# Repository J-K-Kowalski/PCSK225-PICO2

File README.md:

# PCSK225-PICO2 SDR Receiver

<ul>
<li>2025-08-27 - Documentation</li>
<li>2025-02-25 - First version of the project</li>
</ul>

## Overview

<p>PCSK225-PICO2 is a compact, low‑cost software defined receiver designed to decode the 225 kHz Polish time signal transmitted from Solec Kujawski. The design is built around the Raspberry Pi Pico 2 (RP2350) module and supports two signal acquisition paths:

- Direct sampling with a high‑speed external ADC (ADS7049)
- Optional SSB down‑conversion using a Si4537‑D60 tuner, enabling baseband sampling with the RP2350’s internal ADC

<p>The board integrates a precision RTC, local display, I/O expansion, audio output, and multiple user I/Os, making it a self‑contained platform for time‑signal experiments and SDR development.

## Key Features

- MCU: Raspberry Pi Pico 2 (RP2350) module
- Direct RF sampling: ADS7049 12‑bit, high‑speed SPI ADC connected to the RP2350 (supports ~225 kHz IF/baseband sampling)
- Optional tuner: Si4537‑D60 for SSB-style down‑conversion to low IF/baseband for sampling by the RP2350 internal ADC
- RF front end:
    - Active 6‑pole Butterworth band‑pass amplifier around TLV9064 (U2) centered on 225 kHz
    - Output/driver amplifier for Si4537 based on TLV9062 (U1)
    - TMUX1204 analog multiplexer (IC1) for flexible signal routing between ADCs and front‑end nodes
- Timing: DS3231 RTC with CR2032 backup battery for stable timekeeping and 1 Hz/32 kHz outputs
- Displays:
    - On‑board 0.96" I2C OLED (SSD1306)
    - Header for an external graphic LCD
- I/O expansion and storage:
    - PCA9500 I2C port expander with integrated EEPROM for configuration storage
- Connectivity and power:
    - Micro‑USB (Pico 2)
    - USB‑C connector for powering the receiver and PC connectivity
- User I/O:
    - 8 general‑purpose digital I/O lines on headers
    - PWM‑driven speaker/buzzer output with buffer stage
- Form factor: single PCB with Pico 2 module, mounting holes, and on‑board connectors
- See pcb.jpg for a 3D view of the assembled board

## Signal Paths

- Direct 225 kHz path:

1) Antenna/RF input → active BPF (U2 TLV9064) → analog mux (IC1) → ADS7049 → RP2350 via SPI/DMA
2) Intended for coherent sampling/decoding of the Polish 225 kHz time code
- Optional SSB/down‑conversion path:

1) RF input → Si4537‑D60 → low‑IF/baseband → output amplifier (U1 TLV9062) → RP2350 internal ADC
2) Useful for alternative demodulation modes and experiments

## Subsystem Details

- Active BPF: 6‑pole Butterworth around 225 kHz using TLV9064 quad op‑amp, input protection, and gain‑setting network
- Analog MUX: TMUX1204 routes filtered RF to the external ADC or other measurement points
- External ADC: ADS7049 low‑latency, SPI, suited for continuous streaming to RP2350 (DMA recommended)
- RTC: DS3231SN provides INT/SQW and 32 kHz outputs; backed by CR2032 cell
- Displays:
    - SSD1306 OLED on I2C bus (address configurable via jumpers)
    - External LCD header with SPI/I2C signals as routed on the schematic
- I2C Expander/EEPROM: PCA9500 provides extra GPIO and non‑volatile storage for calibration and user settings
- Audio: small speaker output driven from MCU PWM through a buffer (74LVC1G34) and filtering
- Power:
    - 3V3 rail with local decoupling (X5R/COG capacitors as noted)
    - USB‑C and Micro‑USB power options; VSYS routed to Pico 2
    - Ferrite bead and RC elements for analog rail cleanliness

## Firmware Notes

- Platform: Arduino core for RP2040/RP2350 or Pico SDK (C/C++)
- Recommended peripherals:
    - SPI DMA for ADS7049 streaming
    - PIO or timers for precise sampling clocks if needed
    - I2C for OLED, RTC, and PCA9500
    - PWM for speaker/buzzer output
- Example tasks:
    - 225 kHz band‑limited sampling and digital demodulation/decoding (e‑Czas/time code)
    - SSB/low‑IF capture via Si4537 with on‑chip ADC
    - UTC timekeeping using DS3231 and PPS alignment

## Connectors and Interfaces

- Pico 2 module header exposes GP0…GP21, ADC pins, SWD, 3V3, VBUS, VSYS
- OLED I2C header and external LCD header
- USB‑C and Micro‑USB
- 8x GPIO header for user applications
- RF input and test headers as shown on the schematic
- Speaker/buzzer connector

## Bill of Main ICs

- RP2350 (Raspberry Pi Pico 2 module)
- ADS7049 (external high‑speed ADC)
- Si4537‑D60 (optional tuner/down‑converter)
- TLV9064 (quad op‑amp, BPF and buffering)
- TLV9062 (dual op‑amp, output driver)
- TMUX1204 (analog multiplexer)
- DS3231SN (RTC)
- PCA9500 (I2C GPIO expander + EEPROM)
- SSD1306 (OLED controller)

## Status

- Hardware: Rev. 2 schematic/PCB
- Image: see pcb.jpg for the assembled PCB render
- Firmware: work in progress

## License

- Hardware and firmware: A permissive license similar to the BSD 2-Clause License, but with a 3rd clause that prohibits others from using the name of the copyright holder or its contributors to promote derived products without written consent.

## Acknowledgements

- Designed by <b>KJK Innovations</b> for research and development of low‑frequency time‑signal receivers and SDR experimentation.

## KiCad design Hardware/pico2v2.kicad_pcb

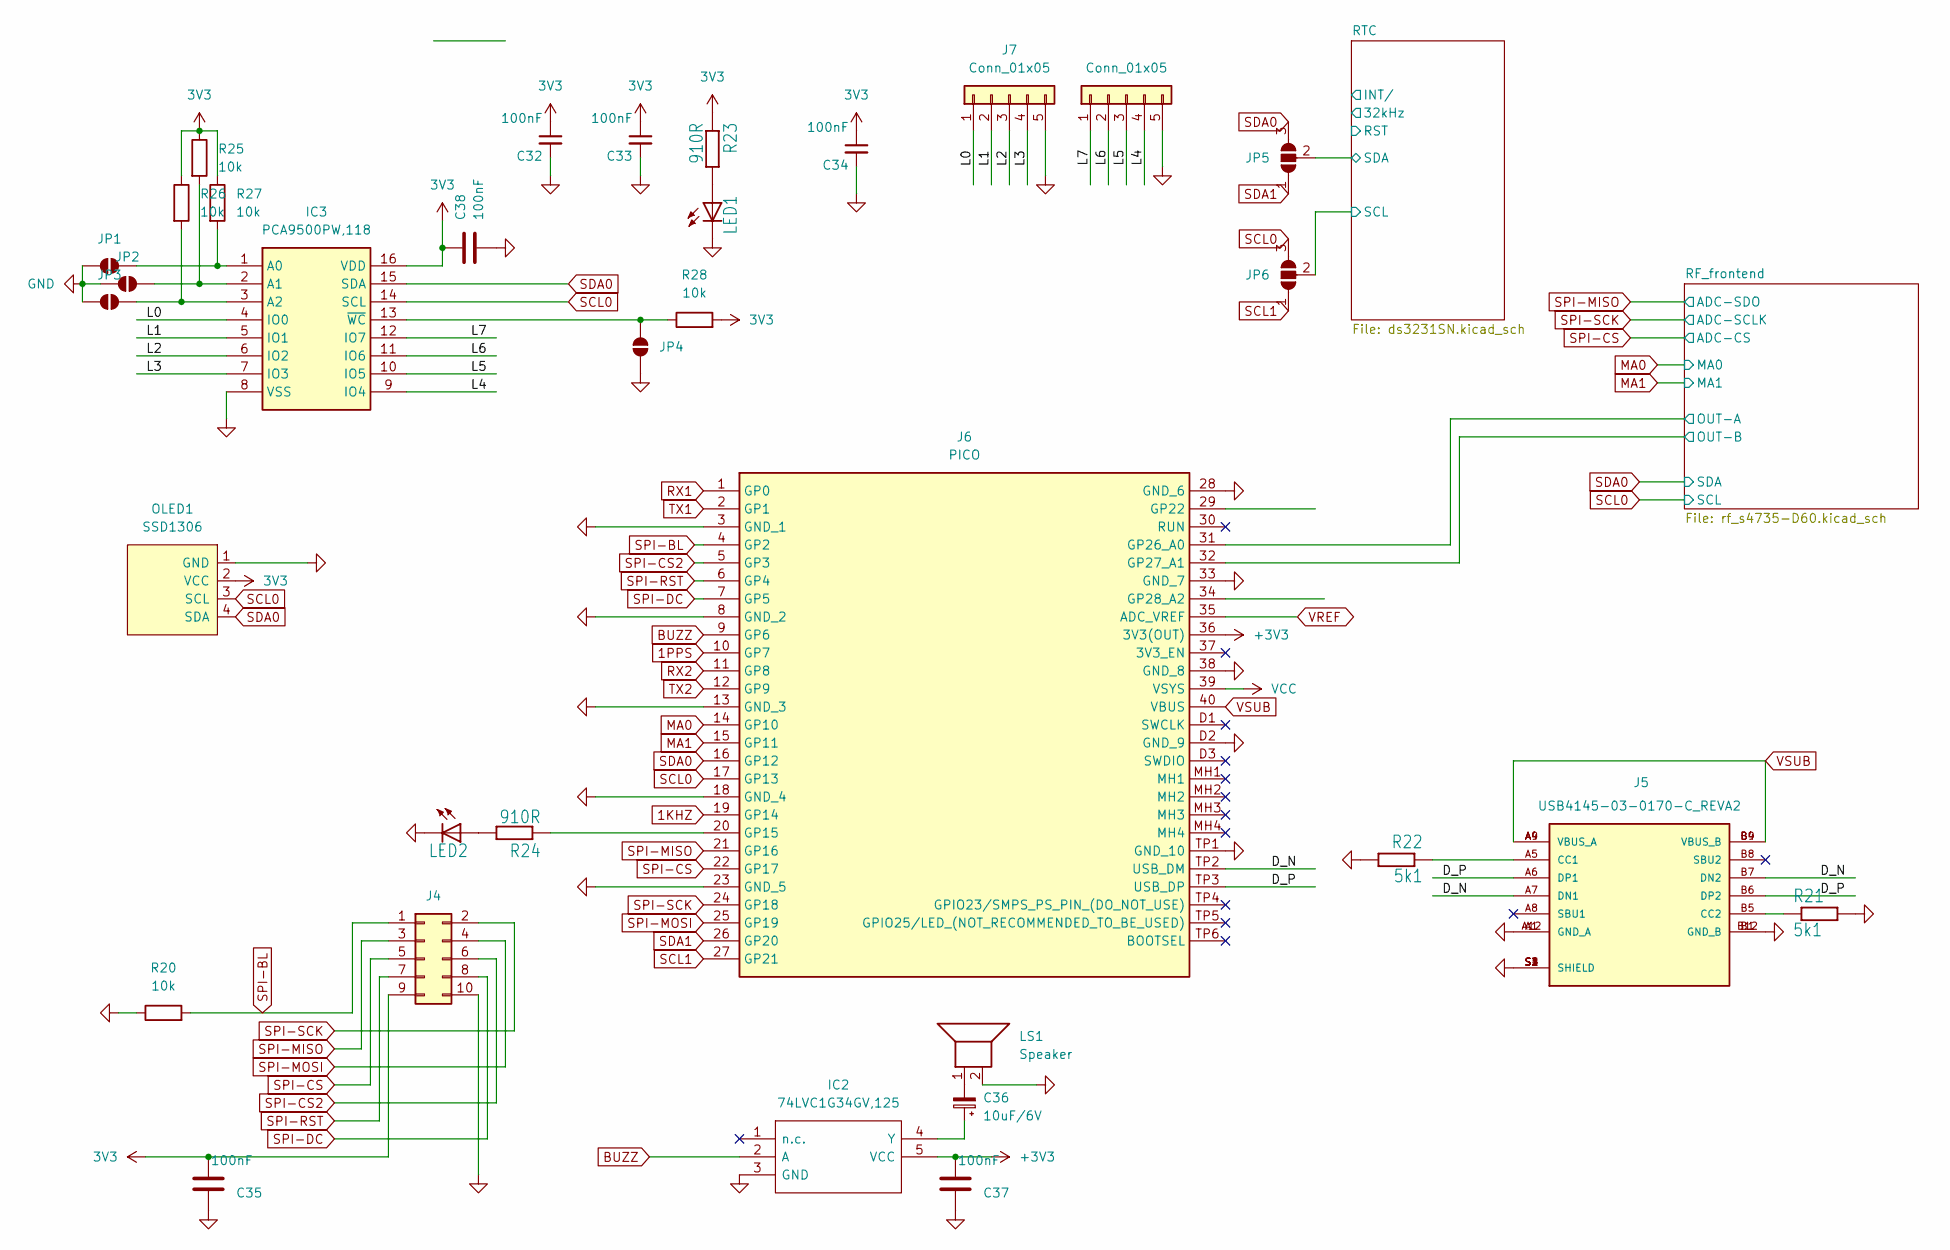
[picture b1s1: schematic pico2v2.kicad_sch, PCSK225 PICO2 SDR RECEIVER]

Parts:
C32, C33, C34, C35, C37, C38: 100nF; C_0603_1608Metric_Pad1.08x0.95mm_HandSolder
C36: 10uF/6V; C_0805_2012Metric_Pad1.18x1.45mm_HandSolder
Connector_PinHeader_2.54mm:PinHeader_1x05_P2.54mm_Vertical1: Conn_01x05; PinHeader_1x05_P2.54mm_Vertical
IC2: 74LVC1G34GV,125; SOT95P275X110-5N; Manufacturer_Part_Number 74LVC1G34GV,125; Mouser Part Number 771-LVC1G34GV125
IC3: PCA9500PW,118; SOP65P640X110-16N; Mouser Part Number 771-PCA9500PW-T
J4: Conn_02x05_Odd_Even; PinHeader_2x05_P2.54mm_Vertical
J5: USB4145-03-0170-C_REVA2; GCT_USB4145-03-0170-C_REVA2; PARTREV A2
J6: PICO; Manufacturer_Part_Number PICO
J7: Conn_01x05; PinHeader_1x05_P2.54mm_Vertical
JP1, JP2, JP3, JP4: SolderJumper_2_Open; SolderJumper-2_P1.3mm_Open_RoundedPad1.0x1.5mm
JP5, JP6: SolderJumper_3_Open; SolderJumper-3_P1.3mm_Open_RoundedPad1.0x1.5mm
LED1, LED2: LEDCHIPLED_0805; CHIP-LED0805
LS1: Speaker; PinSocket_1x02_P2.54mm_Vertical
OLED1: SSD1306; 128x64OLED
R20, R25, R26, R27, R28: 10k; R_0603_1608Metric_Pad0.98x0.95mm_HandSolder
R21, R22: 5k1; R_0603_1608Metric_Pad0.98x0.95mm_HandSolder
R23, R24: 910R; R_0603_1608Metric_Pad0.98x0.95mm_HandSolder

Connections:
1KHZ: J6.19 (GP14)
1PPS: J6.10 (GP7)
3V3: C32.1, C33.1, C34.1, C35.2, C38.1, IC3.16 (VDD), J4.9, OLED1.2 (VCC), R23.1, R25.1, R26.1, R27.1, R28.2; also elsewhere on the board
+3V3: C37.2, IC2.5 (VCC), J6.36 (3V3(OUT))
/D_N: J5.A7 (DN1), J5.B7 (DN2), J6.42, J6.TP2 (USB_DM)
/D_P: J5.A6 (DP1), J5.B6 (DP2), J6.42, J6.TP3 (USB_DP)
/L0: IC3.4 (IO0), J7.1
/L1: IC3.5 (IO1), J7.2
/L2: IC3.6 (IO2), J7.3
/L3: IC3.7 (IO3), J7.4
/L4: Connector_PinHeader_2.54mm:PinHeader_1x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.4, IC3.9 (IO4)
/L5: Connector_PinHeader_2.54mm:PinHeader_1x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.3, IC3.10 (IO5)
/L6: Connector_PinHeader_2.54mm:PinHeader_1x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.2, IC3.11 (IO6)
/L7: Connector_PinHeader_2.54mm:PinHeader_1x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.1, IC3.12 (IO7)
/RF_frontend/OUT-A: J6.31 (GP26_A0); also elsewhere on the board
/RF_frontend/OUT-B: J6.32 (GP27_A1); also elsewhere on the board
/RTC/SCL: JP6.2 (C); also elsewhere on the board
/RTC/SDA: JP5.2 (C); also elsewhere on the board
BUZZ: IC2.2 (A), J6.9 (GP6)
GND: C32.2, C33.2, C34.2, C35.1, C37.1, C38.2, Connector_PinHeader_2.54mm:PinHeader_1x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.5, IC2.3 (GND), IC3.8 (VSS), J4.10, J5.A1 (GND_A), J5.A12 (GND_A), J5.B1 (GND_B), J5.B12 (GND_B), J5.S1 (SHIELD), J5.S2 (SHIELD), J5.S3 (SHIELD), J5.S4 (SHIELD), J6.3 (GND_1), J6.8 (GND_2), J6.13 (GND_3), J6.18 (GND_4), J6.23 (GND_5), J6.28 (GND_6), J6.33 (GND_7), J6.38 (GND_8), J6.42, J6.D2 (GND_9), J6.TP1 (GND_10), J7.5, JP1.2 (B), JP2.2 (B), JP3.2 (B), JP4.2 (B), LED1.C, LED2.C, LS1.2, OLED1.1 (GND), R20.1, R21.2, R22.2; also elsewhere on the board
MA0: J6.14 (GP10); also elsewhere on the board
MA1: J6.15 (GP11); also elsewhere on the board
unnamed: C36.2, LS1.1
unnamed: C36.1, IC2.4 (Y)
unnamed: IC3.1 (A0), JP1.1 (A), R27.2
unnamed: IC3.2 (A1), JP2.1 (A), R25.2
unnamed: IC3.3 (A2), JP3.1 (A), R26.2
unnamed: IC3.13 (~WC), JP4.1 (A), R28.1
unnamed: J5.A5 (CC1), R22.1
unnamed: J5.B5 (CC2), R21.1
unnamed: J6.20 (GP15), R24.1
unnamed: LED1.A, R23.2
unnamed: LED2.A, R24.2
RX1: J6.1 (GP0)
RX2: J6.11 (GP8)
SCL0: IC3.14 (SCL), J6.17 (GP13), JP6.3 (B), OLED1.3 (SCL); also elsewhere on the board
SCL1: J6.27 (GP21), JP6.1 (A)
SDA0: IC3.15 (SDA), J6.16 (GP12), JP5.3 (B), OLED1.4 (SDA); also elsewhere on the board
SDA1: J6.26 (GP20), JP5.1 (A)
SPI-BL: J4.1, J6.4 (GP2), R20.2
SPI-CS: J4.5, J6.22 (GP17); also elsewhere on the board
SPI-CS2: J4.6, J6.5 (GP3)
SPI-DC: J4.8, J6.7 (GP5)
SPI-MISO: J4.3, J6.21 (GP16); also elsewhere on the board
SPI-MOSI: J4.4, J6.25 (GP19)
SPI-RST: J4.7, J6.6 (GP4)
SPI-SCK: J4.2, J6.24 (GP18); also elsewhere on the board
TX1: J6.2 (GP1)
TX2: J6.12 (GP9)
VCC: J6.39 (VSYS)
VREF: J6.35 (ADC_VREF)
VSUB: J5.A4 (VBUS_A), J5.A9 (VBUS_A), J5.B4 (VBUS_B), J5.B9 (VBUS_B), J6.40 (VBUS)

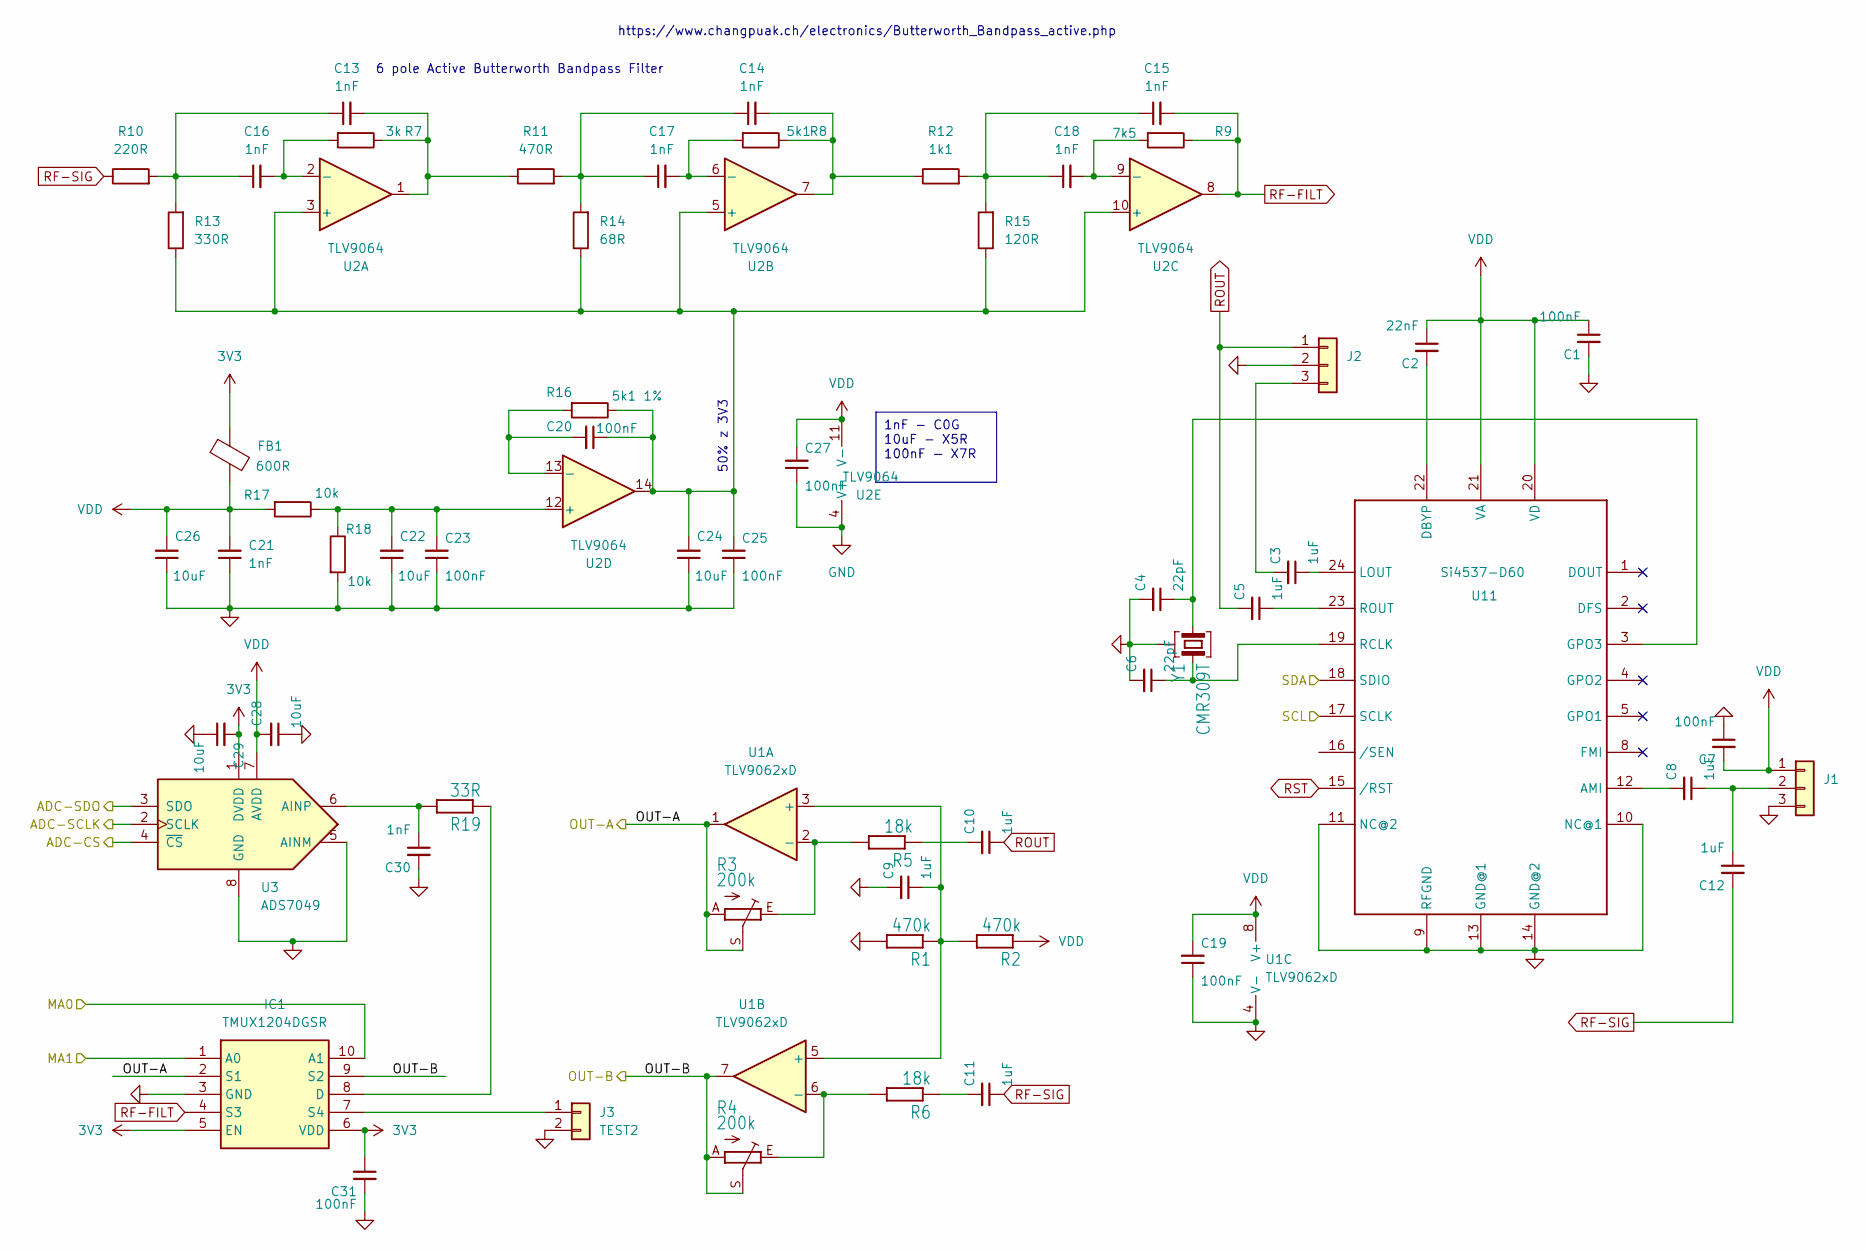
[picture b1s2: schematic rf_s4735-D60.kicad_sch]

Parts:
C1, C7, C19, C20, C23, C25, C27, C31: 100nF; C_0603_1608Metric_Pad1.08x0.95mm_HandSolder
C2: 22nF; C_0603_1608Metric_Pad1.08x0.95mm_HandSolder
C3, C5, C8, C9, C10, C11, C12: 1uF; C_0603_1608Metric_Pad1.08x0.95mm_HandSolder
C4, C6: 22pF; C_0603_1608Metric_Pad1.08x0.95mm_HandSolder
C13, C14, C15, C16, C17, C18, C21, C30: 1nF; C_0603_1608Metric_Pad1.08x0.95mm_HandSolder
C22, C24, C26, C28, C29: 10uF; C_0603_1608Metric_Pad1.08x0.95mm_HandSolder
FB1: 600R; C_0603_1608Metric_Pad1.08x0.95mm_HandSolder
IC1: TMUX1204DGSR; SOP50P490X110-10N; Mouser Part Number 595-TMUX1204DGSR
J1: ANT1; JST_EH_B3B-EH-A_1x03_P2.50mm_Vertical
J2: TEST1; JST_EH_B3B-EH-A_1x03_P2.50mm_Vertical
J3: TEST2; JST_EH_B2B-EH-A_1x02_P2.50mm_Vertical
R1, R2: 470k; R_0603_1608Metric_Pad0.98x0.95mm_HandSolder
R3, R4: 200k; RJ9W
R5, R6: 18k; R_0603_1608Metric_Pad0.98x0.95mm_HandSolder
R7: 3k; R_0603_1608Metric_Pad0.98x0.95mm_HandSolder
R8, R16: 5k1; R_0603_1608Metric_Pad0.98x0.95mm_HandSolder
R9: 7k5; R_0603_1608Metric_Pad0.98x0.95mm_HandSolder
R10: 220R; R_0603_1608Metric_Pad0.98x0.95mm_HandSolder
R11: 470R; R_0603_1608Metric_Pad0.98x0.95mm_HandSolder
R12: 1k1; R_0603_1608Metric_Pad0.98x0.95mm_HandSolder
R13: 330R; R_0603_1608Metric_Pad0.98x0.95mm_HandSolder
R14: 68R; R_0603_1608Metric_Pad0.98x0.95mm_HandSolder
R15: 120R; R_0603_1608Metric_Pad0.98x0.95mm_HandSolder
R17, R18: 10k; R_0603_1608Metric_Pad0.98x0.95mm_HandSolder
R19: 33R; R_0603_1608Metric_Pad0.98x0.95mm_HandSolder
U1: TLV9062xD; SOIC-8_3.9x4.9mm_P1.27mm
U2: TLV9064; SOIC-14_3.9x8.7mm_P1.27mm
U3: ADS7049; VSSOP-8_2.3x2mm_P0.5mm
U11: Si4537-D60; SSOP-24_3.9x8.7mm_P0.635mm
Y1: CMR309T; Crystal_SMD_MicroCrystal_MS3V-T1R

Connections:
3V3: C29.2, C31.1, FB1.1, IC1.5 (EN), IC1.6 (VDD), U3.1 (DVDD); also elsewhere on the board
/RF_frontend/OUT-A: IC1.2 (S1), R3.A, R3.S, U1.1; also elsewhere on the board
/RF_frontend/OUT-B: IC1.9 (S2), R4.A, R4.S, U1.7; also elsewhere on the board
GND: C1.2, C4.2, C6.2, C7.1, C9.2, C19.1, C21.1, C22.1, C23.1, C24.1, C25.1, C26.1, C27.1, C28.1, C29.1, C30.2, C31.2, IC1.3 (GND), J1.3, J2.2, J3.2, R1.2, R18.2, U1.4 (V-), U2.4 (V+), U3.5 (AINM), U3.8 (GND), U11.9 (RFGND), U11.10 (NC@1), U11.11 (NC@2), U11.13 (GND@1), U11.14 (GND@2), Y1.3 (G); also elsewhere on the board
MA0: IC1.10 (A1); also elsewhere on the board
MA1: IC1.1 (A0); also elsewhere on the board
unnamed: C10.2, R5.1
unnamed: C11.2, R6.1
unnamed: C13.1, C16.1, R10.2, R13.2
unnamed: C13.2, R7.1, R11.1, U2.1
unnamed: C14.1, C17.1, R11.2, R14.2
unnamed: C14.2, R8.1, R12.1, U2.7
unnamed: C15.1, C18.1, R12.2, R15.2
unnamed: IC1.8 (D), R19.1
unnamed: IC1.7 (S4), J3.1
unnamed: C8.1, C12.1, J1.2
unnamed: C3.2, J2.3
unnamed: C9.1, R1.1, R2.2, U1.3 (+), U1.5 (+)
unnamed: R3.E, R5.2, U1.2 (-)
unnamed: R4.E, R6.2, U1.6 (-)
unnamed: C20.1, C24.2, C25.2, R13.1, R14.1, R15.1, R16.1, U2.3 (+), U2.5 (+), U2.10 (+), U2.14
unnamed: C16.2, R7.2, U2.2 (-)
unnamed: C17.2, R8.2, U2.6 (-)
unnamed: C18.2, R9.2, U2.9 (-)
unnamed: C22.2, C23.2, R17.1, R18.1, U2.12 (+)
unnamed: C20.2, R16.2, U2.13 (-)
unnamed: C30.1, R19.2, U3.6 (AINP)
unnamed: C8.2, U11.12 (AMI)
unnamed: C2.2, U11.22 (DBYP)
unnamed: C4.1, U11.3 (GPO3), Y1.1
unnamed: C3.1, U11.24 (LOUT)
unnamed: C6.1, U11.19 (RCLK), Y1.2
unnamed: C5.1, U11.23 (ROUT)
RF-FILT: C15.2, IC1.4 (S3), R9.1, U2.8
RF-SIG: C11.1, C12.2, R10.1
ROUT: C5.2, C10.1, J2.1
RST: U11.15 (/RST)
SCL0: U11.17 (SCLK); also elsewhere on the board
SDA0: U11.18 (SDIO); also elsewhere on the board
SPI-CS: U3.4 (~CS); also elsewhere on the board
SPI-MISO: U3.3 (SDO); also elsewhere on the board
SPI-SCK: U3.2 (SCLK); also elsewhere on the board
VDD: C1.1, C2.1, C7.2, C19.2, C21.2, C26.2, C27.2, C28.2, FB1.2, J1.1, R2.1, R17.2, U1.8 (V+), U2.11 (V-), U3.7 (AVDD), U11.20 (VD), U11.21 (VA)

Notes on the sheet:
1nF - C0G 10uF - X5R 100nF - X7R
https://www.changpuak.ch/electronics/Butterworth_Bandpass_active.php
50% z 3V3
6 pole Active Butterworth Bandpass Filter

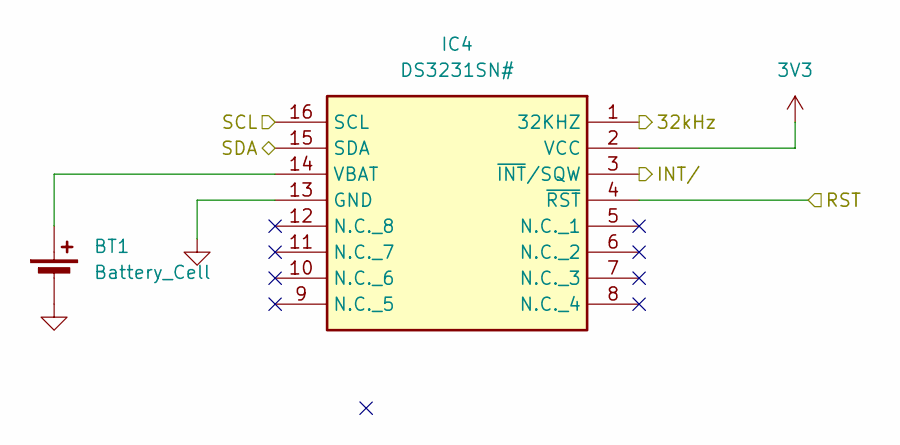
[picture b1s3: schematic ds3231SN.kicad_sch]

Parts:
BT1: Battery_Cell; BatteryHolder_MYOUNG_BS-07-A1BJ001_CR2032
IC4: DS3231SN#; SOIC127P1032X265-16N; Mouser Part Number 700-DS3231SN#

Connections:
3V3: IC4.2 (VCC); also elsewhere on the board
/RTC/32kHz: IC4.1 (32KHZ)
/RTC/INT/: IC4.3 (~INT/SQW)
/RTC/RST: IC4.4 (~RST)
/RTC/SCL: IC4.16 (SCL); also elsewhere on the board
/RTC/SDA: IC4.15 (SDA); also elsewhere on the board
GND: BT1.2 (-), IC4.13 (GND); also elsewhere on the board
unnamed: BT1.1 (+), IC4.14 (VBAT)

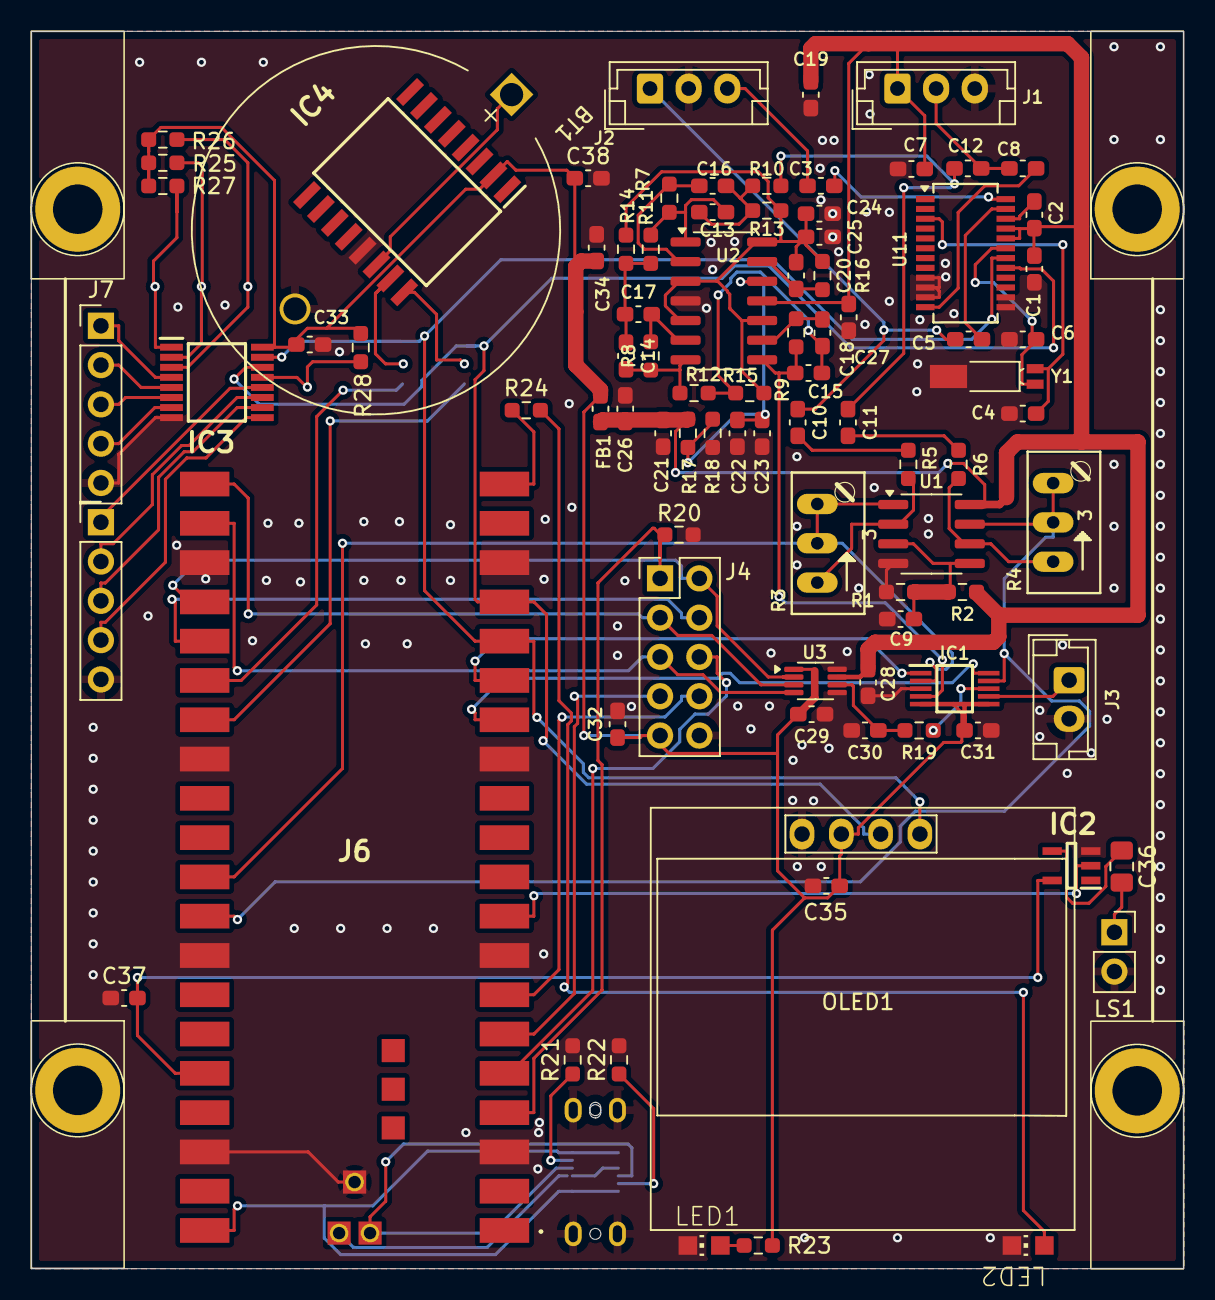
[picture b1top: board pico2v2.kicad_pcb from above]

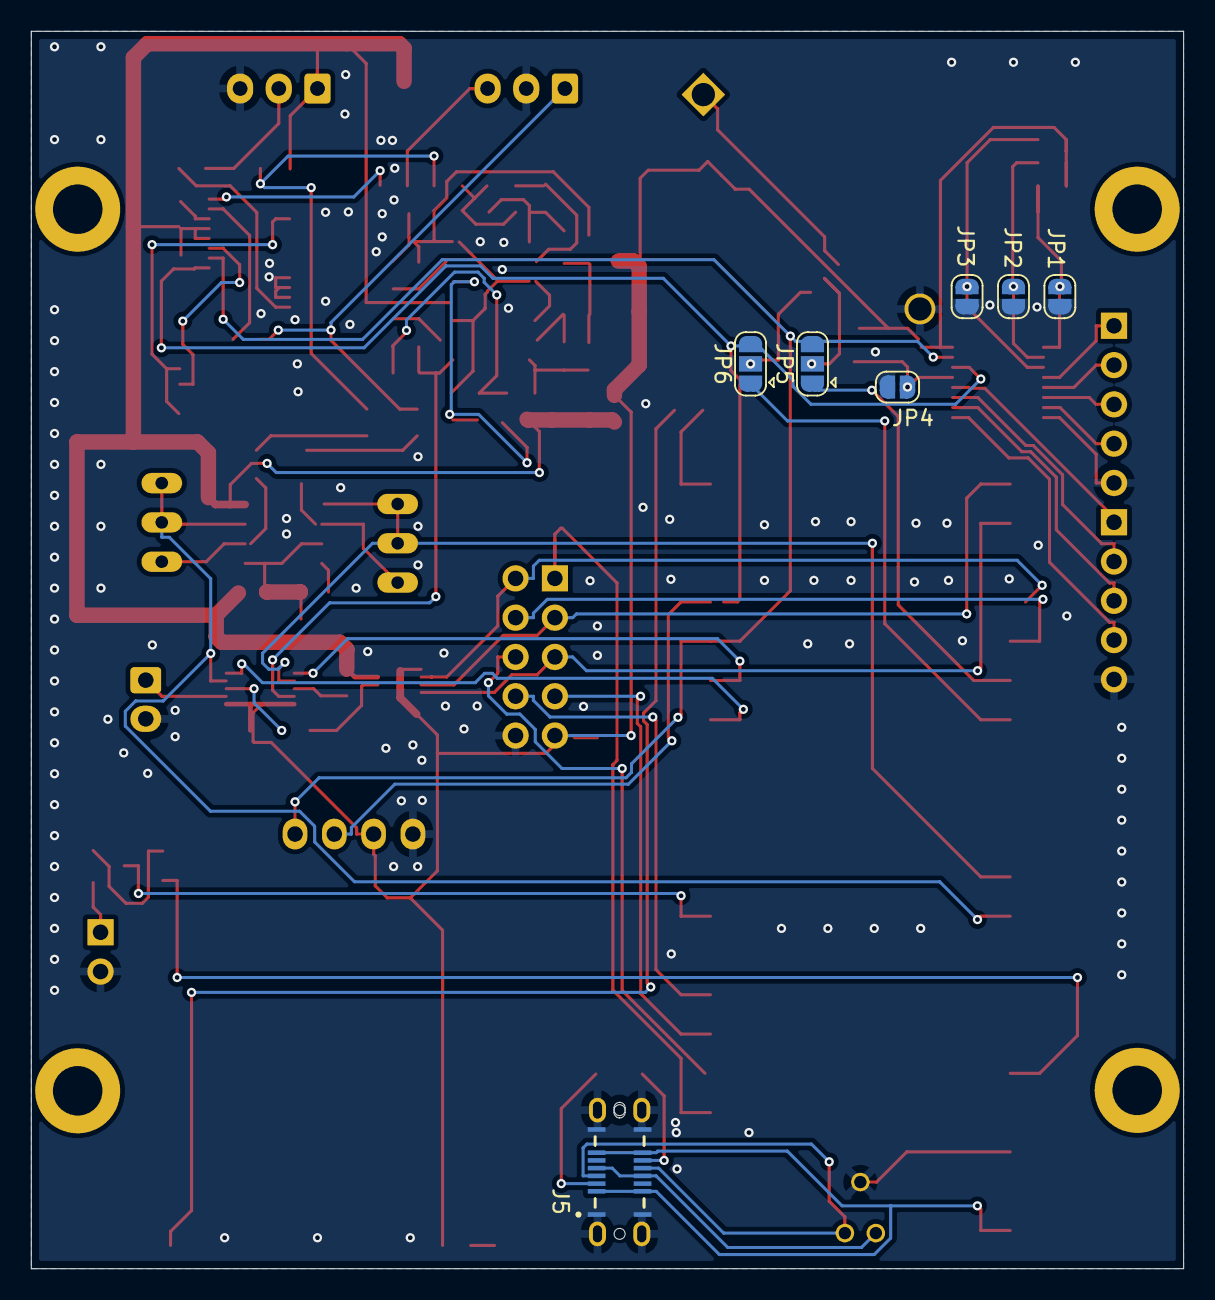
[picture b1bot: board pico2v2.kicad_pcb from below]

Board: 2 copper layers, 74.5 x 80.0 mm, 99 parts (7 on the bottom side), 76 nets.

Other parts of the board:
PMB1, PMB2, PMB3, PMB4: PMB-1

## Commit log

2025-02-01 start version
2025-08-27 more doc
